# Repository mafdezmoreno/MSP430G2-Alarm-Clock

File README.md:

# MSP430G2-Alarm-Clock

## Introduction

## Hardware Requirements

 - MCU: msp430g2553 or similar (with enough memory).
 - External low frequency clock (32768Hz).
 - PCB, proto board, something to build the circuit.
 - Programmer. In my case I'm using the programmer of a launchpad.

Warning: LaunchPads with eZ430-RF2500 will not work with linux or mac, look for launchpads with eZ-FET interface.

### Functions Implemented

 - [X] Clock
 - [X] Date
 - [X] Alarm
 - [X] Control to set clock time and date time.
 - [X] Control to set alarm
 - [X] Battery level monitoring
 - [X] Humidity and temperature with dht sensor
 - [X] Auto lcd light on if some button is pushed
 - [X] Low power mode. This mode reduces minimum power consumption from 0.71mA to 0.33mA

## Compiling the Code

There are two principal compiler options:
 * Ti Compiler, included in [CSStudio IDE](https://www.ti.com/tool/CCSTUDIO) (recommended).
 * [GNU Compiler](https://www.ti.com/tool/MSP430-GCC-OPENSOURCE) 

The best way to avoid problems is use CSStudio and Ti compiler. Trying another options can ba a frustrating process.

Anyway, I prefer to generate/update the makefile with CSS and then work with Clion or VSCode.

I've also tried to create a cMake projects, based on [AlexanderSidorenko repo](https://github.com/AlexanderSidorenko/msp-cmake), but with no success by now.

## Flashing the MCU
There are several tools to flash the compiled code into the MSC:
 * Code Composer Studio, which uses internally MSP430Flasher (recommended).
 * [MSP430Flasher](https://www.ti.com/tool/MSP430-FLASHER) cl software and your favourite text editor (more work). A 'upload' make argument can be manually placed inside the CSS generated makefile.
 * [mspdebuger](https://dlbeer.co.nz/mspdebug/). This was my favourite in the past, but I was unable to make in work, maybe mspdebuger is not compatible with current TI compiler.

[More info about upload code using MSP430Flasher here](https://github.com/mafdezmoreno/Testing_MSP430G2)

### Hardware Connections:

Connect the following signals from the debugger to the target MCU.

 * 3.3V
 * GND
 * SBWTDIO
 * SBWTCK

## Schematics and PCB

A Kicad project is included in this repo. This projects include schematics and PCB.

Todo:
 - [X] Review of connections
 - [X] PCB Design
 - [X] Gerber files generation and PCB ordering.

## Other Comments and Problems Working With MSP430

The real time operations can be affected for encapsulation and compiler configuration and introduce in the compiled code unexpected delays. The solution can involve simplify the code (reduce encapsulation to make it "easier" to the compiler) and/or tune the compiler settings.

# Useful resources

 - [MSP430F2xx, MSP430G2xx Family User’s Guide](https://www.ti.com/lit/ug/slau144k/slau144k.pdf?ts=1694900974657&ref_url=https%253A%252F%252Fwww.ti.com%252Fproduct%252FMSP430F2418)
 - [MSP Flasher User’s Guide](https://www.ti.com/lit/ug/slau654e/slau654e.pdf?ts=1694985823973&ref_url=https%253A%252F%252Fwww.google.com%252F)
 - [MSP430 Optimizing C/C++ Compiler v21.6.0.LTS](https://www.ti.com/lit/ug/slau132y/slau132y.pdf?ts=1695037938667)
 - [MSP430G2x53 datasheet](https://www.ti.com/lit/ds/symlink/msp430g2553.pdf?ts=1695283635994&ref_url=https%253A%252F%252Fwww.ti.com%252Fproduct%252FMSP430G2553)

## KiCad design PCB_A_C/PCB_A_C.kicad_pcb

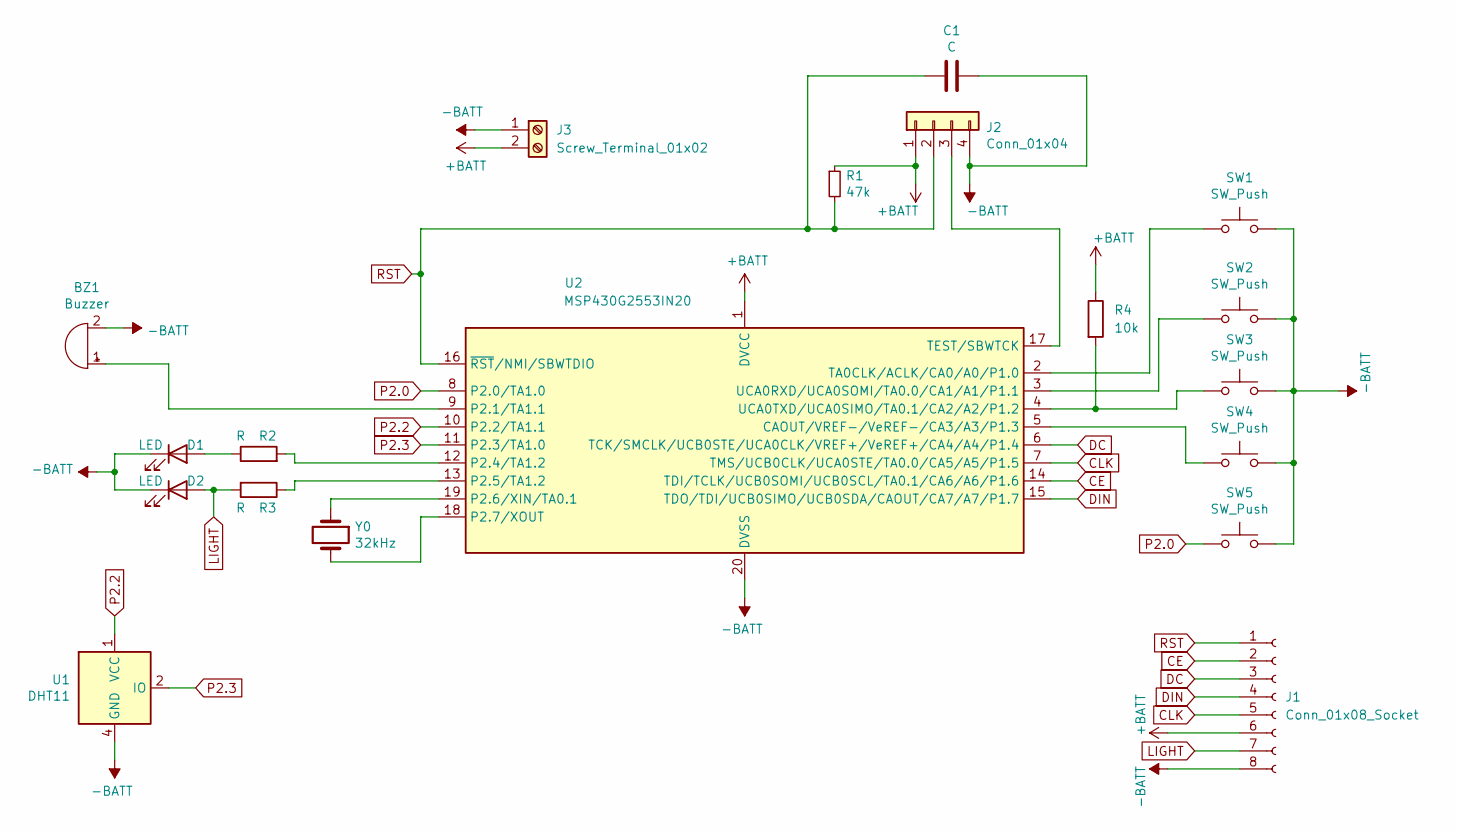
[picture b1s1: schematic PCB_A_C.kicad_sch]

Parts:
BZ1: Buzzer; Buzzer_12x9.5RM7.6
C1: C; CP_Radial_D4.0mm_P2.00mm
D1, D2: LED; LED_D3.0mm
J1: Conn_01x08_Socket; PinSocket_1x08_P2.54mm_Vertical
J2: Conn_01x04; PinSocket_1x04_P2.54mm_Vertical
J3: Screw_Terminal_01x02; TerminalBlock_MetzConnect_Type101_RT01602HBWC_1x02_P5.08mm_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
R1: 47k; R_1210_3225Metric_Pad1.30x2.65mm_HandSolder
R2, R3: R; R_1210_3225Metric_Pad1.30x2.65mm_HandSolder
R4: 10k; R_1210_3225Metric_Pad1.30x2.65mm_HandSolder
SW1, SW2, SW3, SW4, SW5: SW_Push; SW_PUSH_6mm
U1: DHT11; Aosong_DHT11_5.5x12.0_P2.54mm
U2: MSP430G2553IN20; DIP-20_W7.62mm
Y0: 32kHz; Crystal_DS26_D2.0mm_L6.0mm_Vertical

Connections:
+BATT: J1.6, J2.1, J3.2, R1.1, R4.1, U2.1 (DVCC)
-BATT: BZ1.2 (+), C1.1, D1.1 (K), D2.1 (K), J1.8, J2.4, J3.1, SW1.2, SW2.2, SW3.2, SW4.2, SW5.2, U1.4 (GND), U2.20 (DVSS)
CE: J1.2, U2.14 (TDI/TCLK/UCB0SOMI/UCB0SCL/TA0.1/CA6/A6/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)
CLK: J1.5, U2.7 (TMS/UCB0CLK/UCA0STE/TA0.0/CA5/A5/P1.5)
DC: J1.3, U2.6 (TCK/SMCLK/UCB0STE/UCA0CLK/VREF+/VeREF+/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)
DIN: J1.4, U2.15 (TDO/TDI/UCB0SIMO/UCB0SDA/CAOUT/CA7/A7/P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)
LIGHT: D2.2 (A), J1.7, R3.2
unnamed: BZ1.1 (-), U2.9 (P2.1/TA1.1)
unnamed: D1.2 (A), R2.1
unnamed: J2.3, U2.17 (TEST/SBWTCK)
unnamed: SW4.1, U2.5 (CAOUT/VREF-/VeREF-/CA3/A3/P1.3)
unnamed: R2.2, U2.12 (P2.4/TA1.2)
unnamed: R3.1, U2.13 (P2.5/TA1.2)
unnamed: U2.19 (P2.6/XIN/TA0.1), Y0.1
unnamed: U2.18 (P2.7/XOUT), Y0.2
unnamed: SW1.1, U2.2 (TA0CLK/ACLK/CA0/A0/P1.0)
unnamed: SW2.1, U2.3 (UCA0RXD/UCA0SOMI/TA0.0/CA1/A1/P1.1)
unnamed: R4.2, SW3.1, U2.4 (UCA0TXD/UCA0SIMO/TA0.1/CA2/A2/P1.2)
P2.0: SW5.1, U2.8 (P2.0/TA1.0)
P2.2: U1.1 (VCC), U2.10 (P2.2/TA1.1)
P2.3: U1.2 (IO), U2.11 (P2.3/TA1.0)
RST: C1.2, J1.1, J2.2, R1.2, U2.16 (~RST/NMI/SBWTDIO)

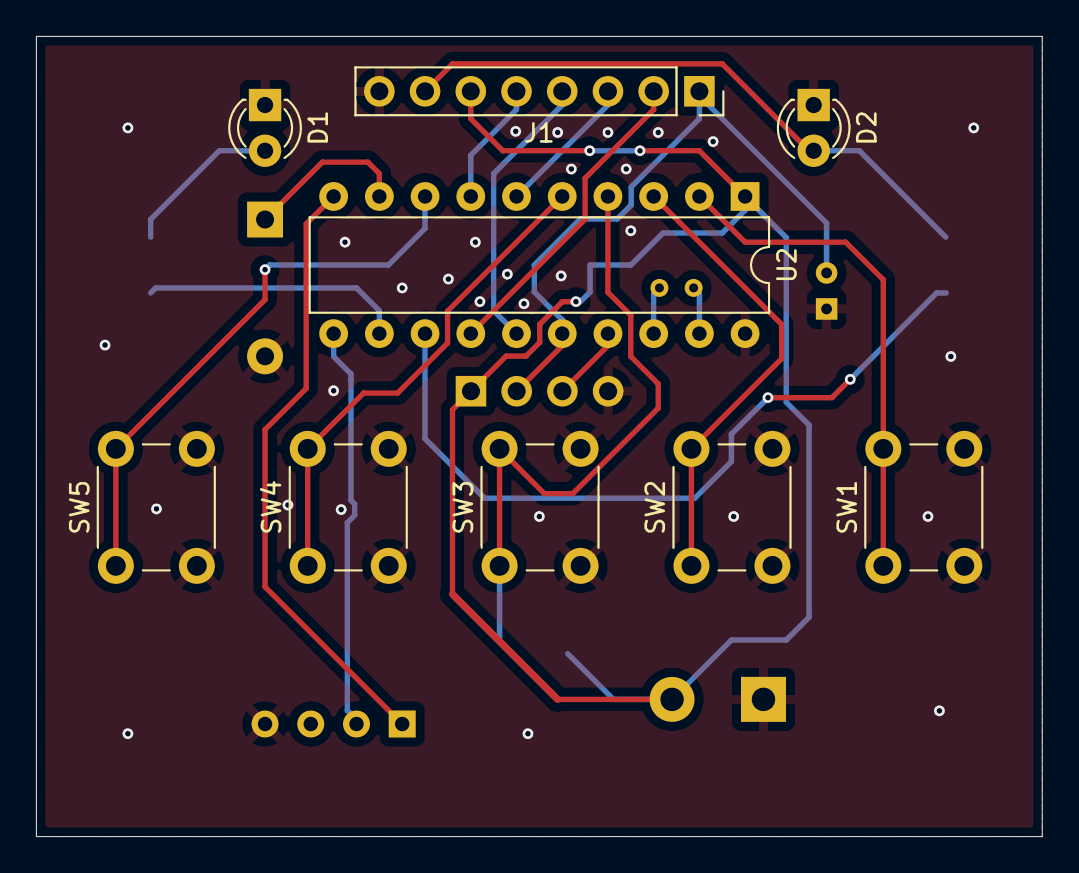
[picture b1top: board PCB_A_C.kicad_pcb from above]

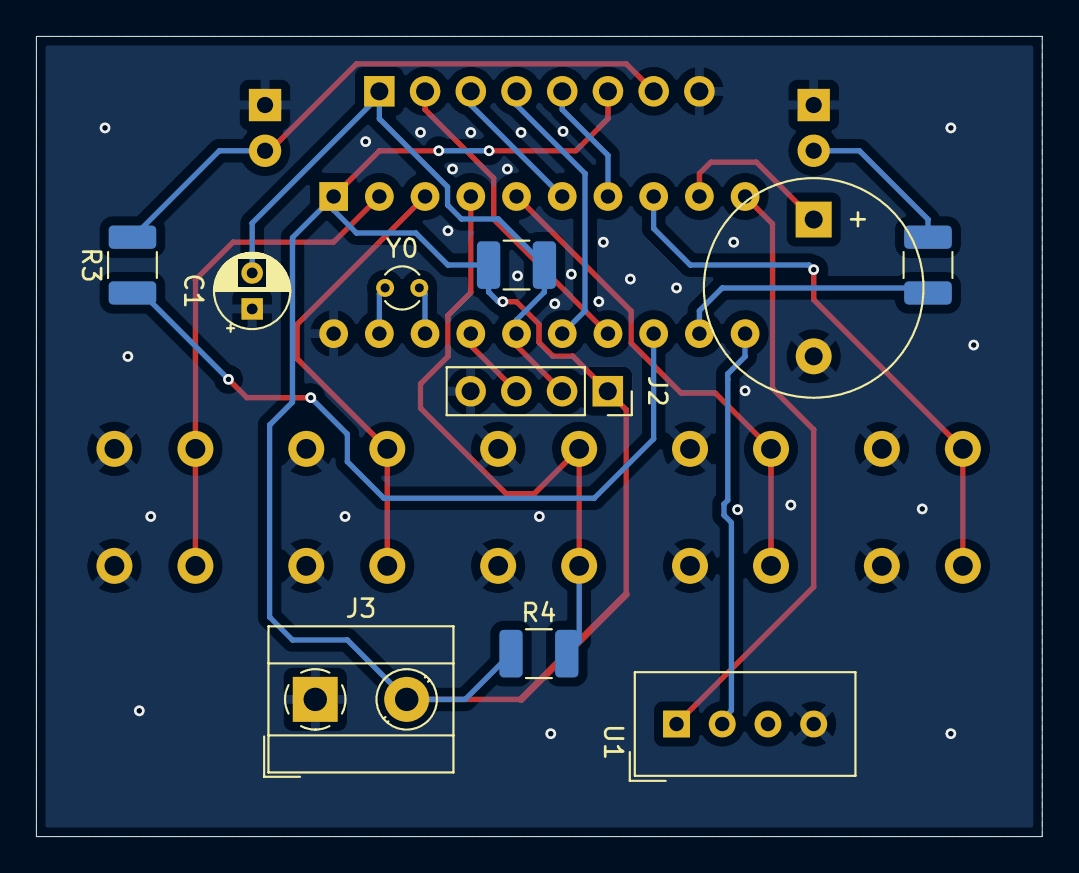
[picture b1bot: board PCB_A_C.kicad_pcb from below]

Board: 2 copper layers, 55.9 x 44.4 mm, 19 parts (10 on the bottom side), 22 nets.

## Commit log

2021-06-12 Initial Version. Based on Testing_MSP430G2/tree/main/Clock_Deb
    Classes implemented.
    Organized structure to continue with the development of the project.
    Only hour value change is implemented.
2021-06-12 Defined positions of values on LCD
2021-06-12 KiCAD Schematic
2023-08-12 Minor changes to move to clion and update compiler
2023-08-14 Initial readme
2023-08-16 MSP430Flasher documentation, commands and links
2023-08-16 code refactoring and style review
2023-08-17 Minor correction, renaming problematic name variables (interference in substitutions)
2023-08-17 CCS makefiles for the current source files
2023-08-17 Integrated timer changes for future buzzer sound alarm functionality.
2023-08-17 Filename and vars name refactored
2023-08-17 Refactoring on time and date class.
2023-08-17 Added buzzer activation class and management to correctly generate the frequency to feed it in callback timer.
2023-08-17 Refactoring on time related variables.
2023-08-17 Completing methods for time and date management
2023-08-18 Actualizar README.md
2023-08-18 Initial scheme for alarm methods
2023-08-18 Refactored button class. Improved delays.
2023-08-18 Improved delay on main loop.
2023-08-18 New mechanism to refresh values on lcd.
2023-08-18 Refactored lcd variables, functions, class and method.
2023-08-18 Corrected eventual unordered date printing.
2023-08-18 Corrected some problems in controls to update date and time. Extended update functionality to all date-time parameters.
2023-08-20 Corrected minors errors on schematic and generated initial PCB version only with components positioned (not routed).
2023-08-21 Routed PCB.
2023-08-22 Corrected connector position on PCB.
2023-08-27 Changes to allow alarm class have access to week day and current time.
2023-08-27 New management for buttons clicks. Implemented initial communication between time, alarm and buttons classes.
2023-08-27 Updated gitignore to include symbolic links. Minor correction.
2023-08-29 Methods on alarm class to send alarm status strings to lcdInterface class.
2023-08-30 Implemented set alarm 1 interface
2023-08-31 Improved (safer) time-date to lcd print
2023-08-31 Seconds don't pause if some button is pushed
2023-08-31 Corrected mechanism to start and stop a preset alarm.
2023-09-02 Cleaning on alarm class. Other minor improvements.
2023-09-02 Including second instance of alarm.
2023-09-03 Including second instance of alarm. Missed changes on last commit.
2023-09-23 New classes/flies. Moved some functions to new files
2023-09-24 Updated make file with new files and commands
2023-09-24 Implemented battery level monitor. Updated readme
2023-09-24 Added timer 1 class
2023-09-24 Added dht sensor to code
2023-09-30 Display led function with auto-deactivation mode
2023-09-30 Clock timer variable recurring interrupts if function of alarms (buzzer) activations.
2023-09-30 Low power mode added. Documented pending tasks.
2023-09-30 Corrected month increment calling
